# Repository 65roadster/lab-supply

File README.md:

# lab-supply
 USB Powered Lab Supply

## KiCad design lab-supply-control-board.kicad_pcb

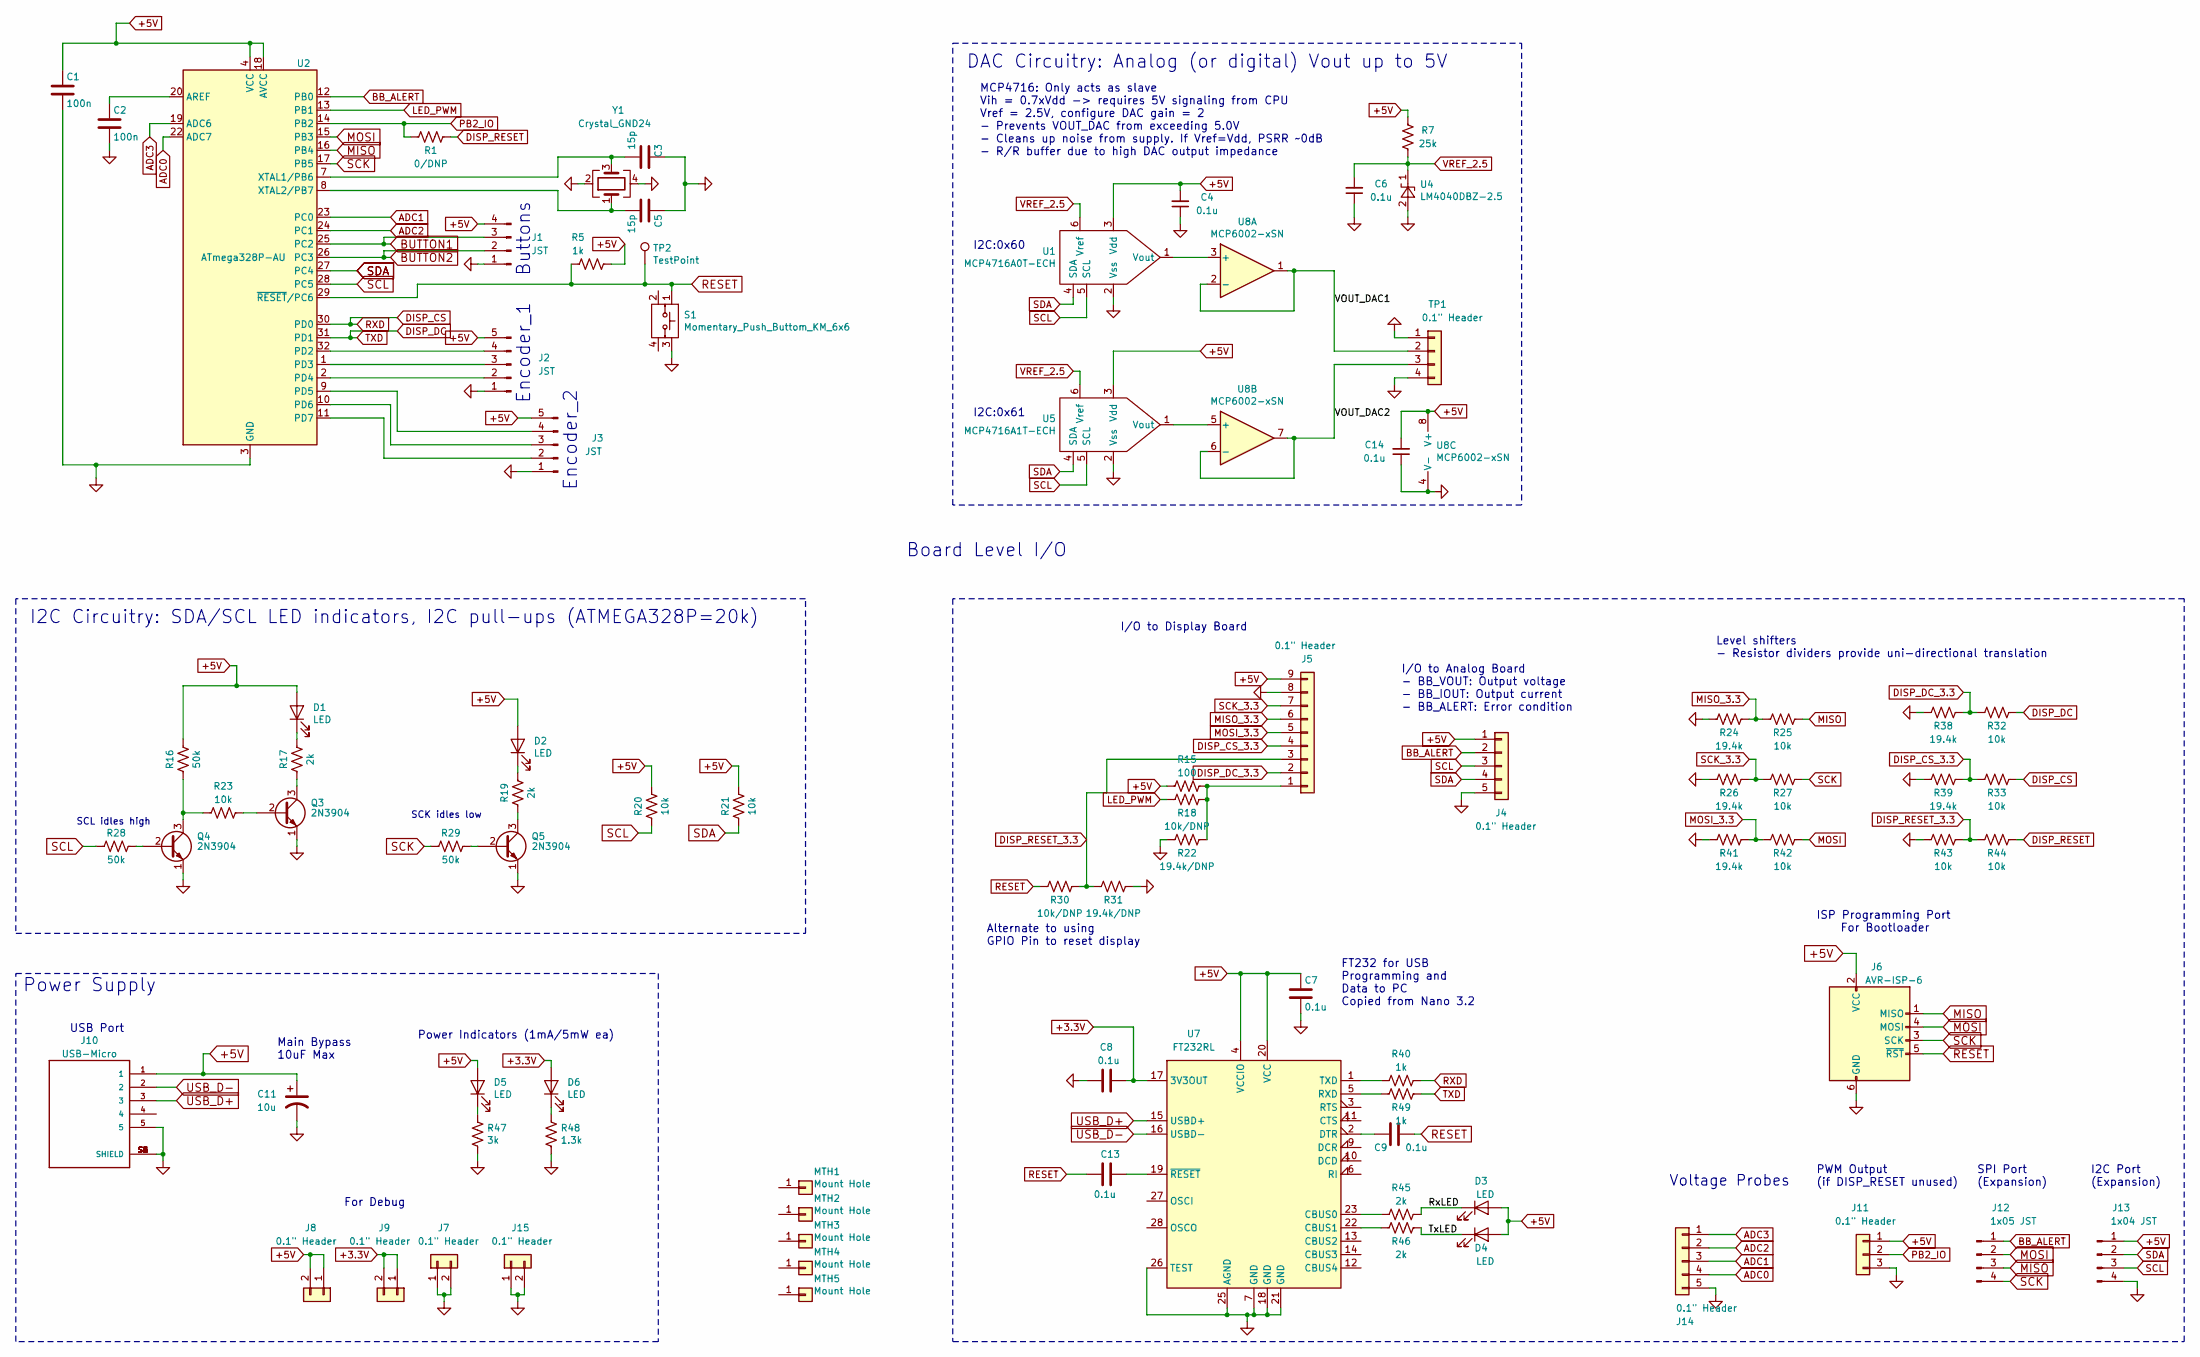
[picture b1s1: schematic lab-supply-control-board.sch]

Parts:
C1, C2: 100n; C_0805_HandSoldering
C3, C5: 15p; C_0603_HandSoldering
C4, C6, C7, C8, C9, C13, C14: 0.1u; C_0805_HandSoldering
C11: 10u; CP_Elec_4x4.5
D1, D2, D3, D4, D5, D6: LED; LED_0805_2012Metric_Pad1.15x1.40mm_HandSolder
J1: JST; JST_XH_B4B-XH-A_1x04_P2.50mm_Vertical
J2, J3: JST; JST_XH_B5B-XH-A_1x05_P2.50mm_Vertical
J4, J14: 0.1\" Header; JST_XH_B5B-XH-A_1x05_P2.50mm_Vertical
J5: 0.1\" Header; JST_XH_B9B-XH-A_1x09_P2.50mm_Vertical
J6: AVR-ISP-6; AVR-ISP-6-TH
J7, J8, J9, J15: 0.1\" Header; PinHeader_1x02_P2.54mm_Vertical
J10: USB-Micro; USB-Micro-AMPHENOL_10118194-0001LF
J11: 0.1\" Header; PinHeader_1x03_P2.54mm_Vertical
J12: 1x05 JST; JST_XH_B4B-XH-A_1x04_P2.50mm_Vertical
J13: 1x04 JST; JST_XH_B4B-XH-A_1x04_P2.50mm_Vertical
MTH1, MTH2, MTH3, MTH4, MTH5: Mount Hole; Mount-Hole-#6
Q3, Q4, Q5: 2N3904; 2N3904-SOT-23
R1: 0/DNP; R_0805_HandSoldering
R5, R40, R49: 1k; R_0805_HandSoldering
R7: 25k; R_0805_HandSoldering
R15: 100; R_0805_HandSoldering
R16, R28, R29: 50k; R_0805_HandSoldering
R17, R19, R45, R46: 2k; R_0805_HandSoldering
R18, R30: 10k/DNP; R_0805_HandSoldering
R20, R21, R23, R25, R27, R32, R33, R42, R43, R44: 10k; R_0805_HandSoldering
R22, R31: 19.4k/DNP; R_0805_HandSoldering
R24, R26, R38, R39, R41: 19.4k; R_0805_HandSoldering
R47: 3k; R_0805_HandSoldering
R48: 1.3k; R_0805_HandSoldering
S1: Momentary_Push_Buttom_KM_6x6; Momentary_Push_Button_KM_6x6
TP1: 0.1\" Header; JST_XH_B4B-XH-A_1x04_P2.50mm_Vertical
TP2: TestPoint; PinHeader_1x01_P2.54mm_Vertical
U1: MCP4716A0T-ECH; SOT-23-6_Handsoldering
U2: ATmega328P-AU; TQFP-32_7x7mm_P0.8mm
U4: LM4040DBZ-2.5; SOT-23
U5: MCP4716A1T-ECH; SOT-23-6_Handsoldering
U7: FT232RL; SSOP-28_5.3x10.2mm_P0.65mm
U8: MCP6002-xSN; SOP-8_3.9x4.9mm_P1.27mm
Y1: Crystal_GND24; Crystal_SMD_CX2016DB_2.0x1.6mm

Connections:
+3.3V: C8.2, D6.2 (A), J9.1, J9.2, U7.17 (3V3OUT)
+5V: C1.1, C4.2, C7.1, C11.1, C14.2, D1.2 (A), D2.2 (A), D3.2 (A), D4.2 (A), D5.2 (A), J1.4, J2.5, J3.5, J4.1, J5.9, J6.2 (VCC), J8.1, J8.2, J10.1, J11.1, J13.1, R5.2, R7.2, R15.1, R16.1, R20.2, R21.2, U1.3 (Vdd), U2.4 (VCC), U2.6 (VCC), U2.18 (AVCC), U5.3 (Vdd), U7.4 (VCCIO), U7.20 (VCC), U8.8 (V+)
/RxLED: D3.1 (K), R45.1
/TxLED: D4.1 (K), R46.1
/VOUT_DAC1: TP1.2, U8.1, U8.2 (-)
/VOUT_DAC2: TP1.3, U8.6 (-), U8.7
ADC0: J14.4, U2.22 (ADC7)
ADC1: J14.3, U2.23 (PC0)
ADC2: J14.2, U2.24 (PC1)
ADC3: J14.1, U2.19 (ADC6)
BB_ALERT: J4.2, J12.1, U2.12 (PB0)
BUTTON1: J1.3, U2.25 (PC2)
BUTTON2: J1.2, U2.26 (PC3)
DISP_CS: R33.2, R40.1, U2.30 (PD0)
DISP_CS_3.3: J5.4, R33.1, R39.2
DISP_DC: R32.2, R49.1, U2.31 (PD1)
DISP_DC_3.3: J5.2, R32.1, R38.2
DISP_RESET: R1.2, R44.2
DISP_RESET_3.3: J5.3, R30.2, R31.1, R43.2, R44.1
GND: C1.2, C2.2, C3.1, C4.1, C5.1, C6.1, C7.2, C8.1, C11.2, C14.1, J1.1, J2.1, J3.1, J4.5, J5.8, J6.6 (GND), J7.1, J7.2, J10.5, J10.S1 (SHIELD), J10.S2 (SHIELD), J10.S3 (SHIELD), J10.S4 (SHIELD), J10.S5 (SHIELD), J10.S6 (SHIELD), J11.3, J13.4, J14.5, J15.1, J15.2, Q3.1 (E), Q4.1 (E), Q5.1 (E), R22.1, R24.1, R26.1, R31.2, R38.1, R39.1, R41.1, R43.1, R47.2, R48.2, S1.3, TP1.1, TP1.4, U1.2 (Vss), U2.3 (GND), U2.5 (GND), U2.21 (GND), U4.2 (A), U5.2 (Vss), U7.7 (GND), U7.18 (GND), U7.21 (GND), U7.25 (AGND), U7.26 (TEST), U8.4 (V-), Y1.2, Y1.4
LED_PWM: R18.1, U2.13 (PB1)
MISO: J6.1 (MISO), J12.3, R25.2, U2.16 (PB4)
MISO_3.3: J5.6, R24.2, R25.1
MOSI: J6.4 (MOSI), J12.2, R42.2, U2.15 (PB3)
MOSI_3.3: J5.5, R41.2, R42.1
unnamed: C2.1, U2.20 (AREF)
unnamed: C3.2, U2.7 (XTAL1/PB6), Y1.3
unnamed: C5.2, U2.8 (XTAL2/PB7), Y1.1
unnamed: C9.1, U7.2 (DTR)
unnamed: C13.1, U7.19 (~RESET~)
unnamed: D1.1 (K), R17.2
unnamed: D2.1 (K), R19.2
unnamed: D5.1 (K), R47.1
unnamed: D6.1 (K), R48.1
unnamed: J2.2, U2.2 (PD4)
unnamed: J2.3, U2.1 (PD3)
unnamed: J2.4, U2.32 (PD2)
unnamed: J3.2, U2.11 (PD7)
unnamed: J3.3, U2.10 (PD6)
unnamed: J3.4, U2.9 (PD5)
unnamed: J5.1, R15.2, R18.2, R22.2
unnamed: Q3.2 (B), R23.2
unnamed: Q3.3 (C), R17.1
unnamed: Q4.2 (B), R28.2
unnamed: Q4.3 (C), R16.2, R23.1
unnamed: Q5.2 (B), R29.2
unnamed: Q5.3 (C), R19.1
unnamed: R40.2, U7.1 (TXD)
unnamed: R45.2, U7.23 (CBUS0)
unnamed: R46.2, U7.22 (CBUS1)
unnamed: R49.2, U7.5 (RXD)
unnamed: U1.1 (Vout), U8.3 (+)
unnamed: U5.1 (Vout), U8.5 (+)
PB2_IO: J11.2, R1.1, U2.14 (PB2)
RESET: C9.2, C13.2, J6.5 (~RST), R5.1, R30.1, S1.1, TP2.1, U2.29 (~RESET~/PC6)
SCK: J6.3 (SCK), J12.4, R27.2, R29.1, U2.17 (PB5)
SCK_3.3: J5.7, R26.2, R27.1
SCL: J4.3, J13.3, R20.1, R28.1, U1.5 (SCL), U2.28 (PC5), U5.5 (SCL)
SDA: J4.4, J13.2, R21.1, U1.4 (SDA), U2.27 (PC4), U5.4 (SDA)
USB_D+: J10.3, U7.15 (USBD+)
USB_D-: J10.2, U7.16 (USBD-)
VREF_2.5: C6.2, R7.1, U1.6 (Vref), U4.1 (K), U5.6 (Vref)

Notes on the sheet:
Voltage Probes
Encoder_1
Encoder_2
SCL idles high
SCK idles low
ISP Programming Port For Bootloader
DAC Circuitry: Analog (or digital) Vout up to 5V
SPI Port (Expansion)
I2C Circuitry: SDA/SCL LED indicators, I2C pull-ups (ATMEGA328P=20k)
USB Port
Board Level I/O
I2C Port (Expansion)
I/O to Display Board
MCP4716: Only acts as slave Vih = 0.7xVdd -> requires 5V signaling from CPU Vref = 2.5V, configure DAC gain = 2 - Prevents VOUT_DAC from exceeding 5.0V - Cleans up noise from supply. If Vref=Vdd, PSRR ~~0dB - R/R buffer due to high DAC output impedance
Power Indicators (1mA/5mW ea)
For Debug
PWM Output (if DISP_RESET unused)
I/O to Analog Board - BB_VOUT: Output voltage - BB_IOUT: Output current - BB_ALERT: Error condition
Level shifters - Resistor dividers provide uni-directional translation
Power Supply
Alternate to using GPIO Pin to reset display
Main Bypass 10uF Max
FT232 for USB Programming and Data to PC Copied from Nano 3.2
I2C:0x60
I2C:0x61
Buttons

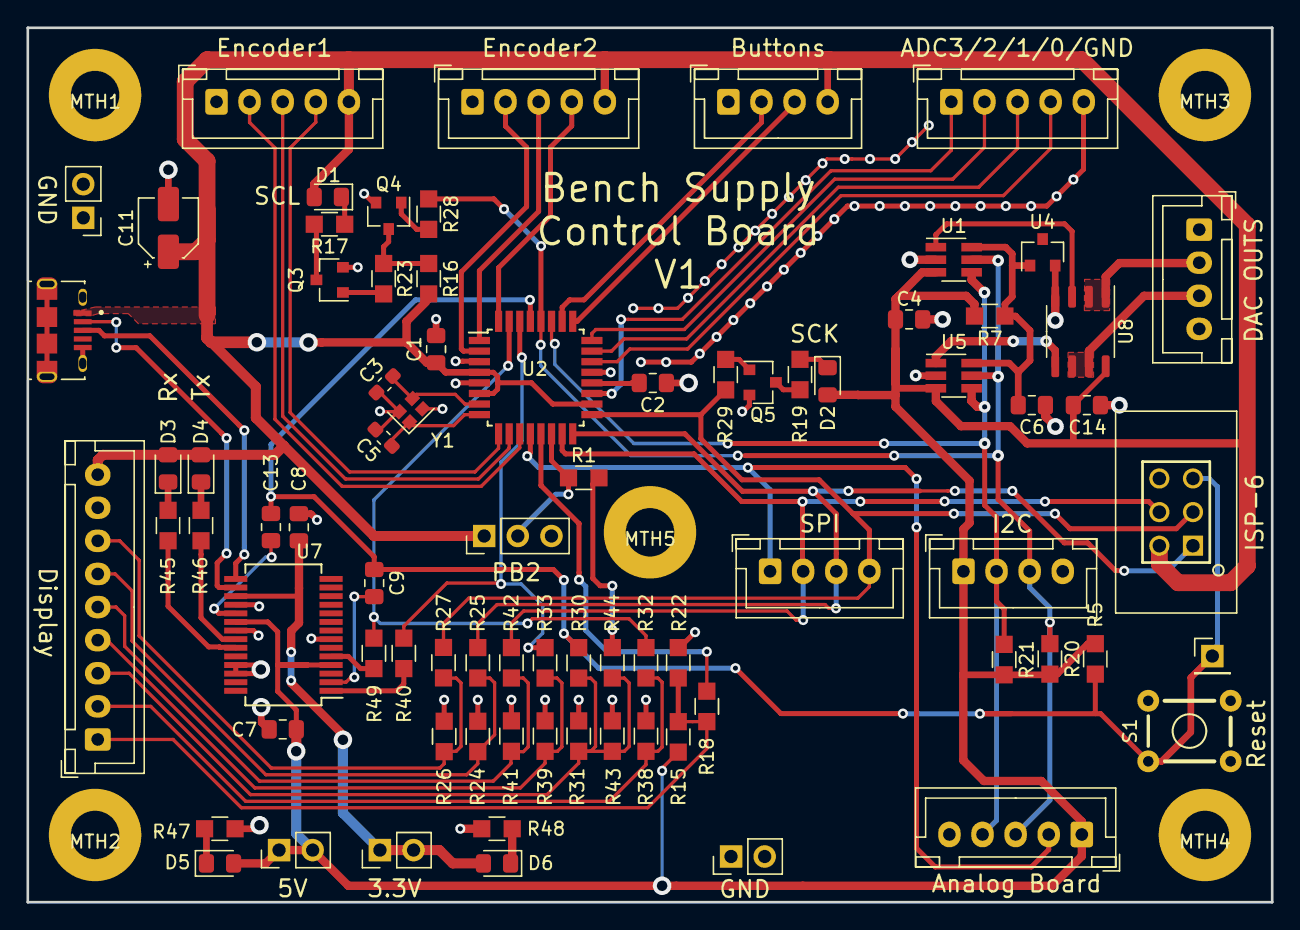
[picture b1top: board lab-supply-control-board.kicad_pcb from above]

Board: 2 copper layers, 94.0 x 66.0 mm, 85 parts (0 on the bottom side), 62 nets.

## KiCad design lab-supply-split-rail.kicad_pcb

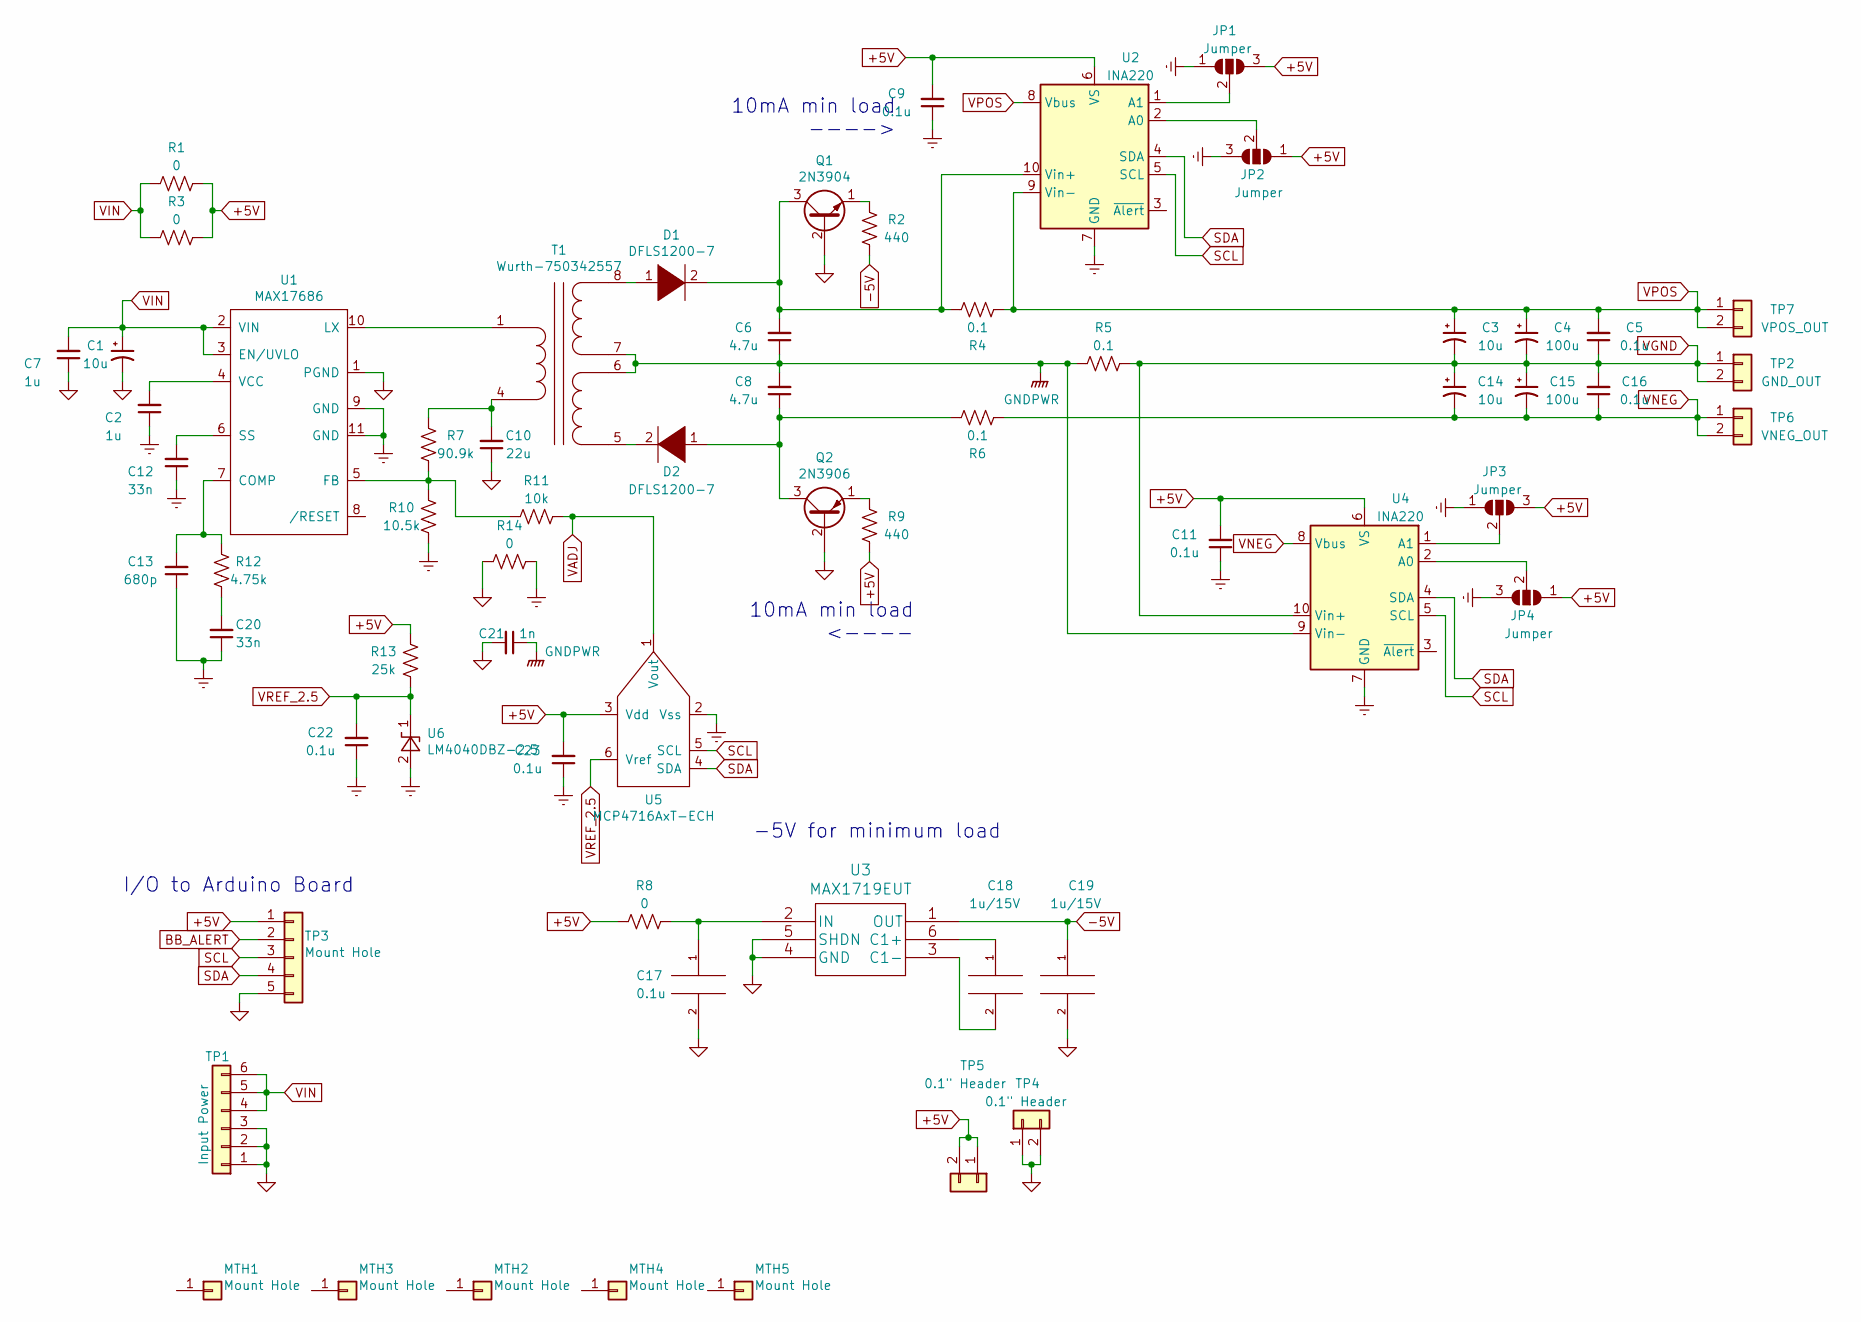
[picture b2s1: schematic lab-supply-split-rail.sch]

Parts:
C1, C3, C14: 10u; CP_Elec_4x4.5
C2, C7: 1u; C_0603_HandSoldering
C4, C15: 100u; CP_Elec_6.3x5.9
C5, C9, C11, C16, C22, C23: 0.1u; C_0603_HandSoldering
C6, C8: 4.7u; C_0603_HandSoldering
C10: 22u; C_0603_HandSoldering
C12, C20: 33n; C_0603_HandSoldering
C13: 680p; C_0603_HandSoldering
C17: 0.1u; C_0805_HandSoldering
C18, C19: 1u/15V; C_0805_HandSoldering
C21: 1n; C_0603_HandSoldering
D1, D2: DFLS1200-7; D_PowerDI-123
JP1, JP2, JP3, JP4: Jumper; SolderJumper_3_Pad
MTH1, MTH2, MTH3, MTH4, MTH5: Mount Hole; Mount-Hole-#6
Q1: 2N3904; SOT-23
Q2: 2N3906; SOT-23
R1, R3, R8, R14: 0; R_0805_HandSoldering
R2, R9: 440; R_0805_HandSoldering
R4, R5, R6: 0.1; R_2512_HandSoldering
R7: 90.9k; R_0805_HandSoldering
R10: 10.5k; R_0805_HandSoldering
R11: 10k; R_0805_HandSoldering
R12: 4.75k; R_0805_HandSoldering
R13: 25k; R_0805_HandSoldering
T1: Wurth-750342557
TP1: Input Power; PinHeader_1x06_P2.54mm_Vertical
TP2: GND_OUT; PinHeader_1x02_P2.54mm_Vertical
TP3: Mount Hole; JST_XH_B5B-XH-A_1x05_P2.50mm_Vertical
TP4, TP5: 0.1\" Header; PinHeader_1x02_P2.54mm_Vertical
TP6: VNEG_OUT; PinHeader_1x02_P2.54mm_Vertical
TP7: VPOS_OUT; PinHeader_1x02_P2.54mm_Vertical
U1: MAX17686; DFN-10-1EP_2x3mm_P0.5mm_EP0.64x2.4mm
U2, U4: INA220; VSSOP-10_3x3mm_P0.5mm
U3: MAX1719EUT; TSOT-23-6_HandSoldering
U5: MCP4716AxT-ECH; SOT-23-6_Handsoldering
U6: LM4040DBZ-2.5; SOT-23

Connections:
+5V: C9.2, C11.2, C23.2, JP1.3 (B), JP2.1 (A), JP3.3 (B), JP4.1 (A), R1.2, R3.2, R8.2, R9.1, R13.2, TP3.1, TP5.1, TP5.2, U2.6 (VS), U4.6 (VS), U5.3 (Vdd)
-5V: C19.1, R2.1, U3.1 (OUT)
Earth: C2.1, C9.1, C11.1, C12.1, C13.1, C20.1, C22.1, C23.1, JP1.1 (A), JP2.3 (B), JP3.1 (A), JP4.3 (B), R10.1, R14.2, U1.9 (GND), U1.11 (GND), U2.7 (GND), U4.7 (GND), U5.2 (Vss), U6.2 (A)
GND: C1.2, C7.1, C10.1, C17.2, C19.2, C21.2, Q1.2 (B), Q2.2 (B), R14.1, TP1.1, TP1.2, TP1.3, TP3.5, TP4.1, TP4.2, U1.1 (PGND), U3.4 (GND), U3.5 (SHDN)
GNDPWR: C6.1, C8.2, C21.1, R5.2, T1.6, T1.7, U4.9 (Vin-)
unnamed: C2.2, U1.4 (VCC)
unnamed: C6.2, D1.2 (A), Q1.3 (C), R4.2, U2.10 (Vin+)
unnamed: C8.1, D2.1 (K), Q2.3 (C), R6.2
unnamed: C10.2, R7.2, T1.4
unnamed: C12.2, U1.6 (SS)
unnamed: C13.2, R12.2, U1.7 (COMP)
unnamed: C17.1, R8.1, U3.2 (IN)
unnamed: C18.1, U3.6 (C1+)
unnamed: C18.2, U3.3 (C1-)
unnamed: C20.2, R12.1
unnamed: D1.1 (K), T1.8
unnamed: D2.2 (A), T1.5
unnamed: JP1.2 (C), U2.1 (A1)
unnamed: JP2.2 (C), U2.2 (A0)
unnamed: JP3.2 (C), U4.1 (A1)
unnamed: JP4.2 (C), U4.2 (A0)
unnamed: Q1.1 (E), R2.2
unnamed: Q2.1 (E), R9.2
unnamed: R7.1, R10.2, R11.1, U1.5 (FB)
unnamed: T1.1, U1.10 (LX)
SCL: TP3.3, U2.5 (SCL), U4.5 (SCL), U5.5 (SCL)
SDA: TP3.4, U2.4 (SDA), U4.4 (SDA), U5.4 (SDA)
VADJ: R11.2, U5.1 (Vout)
VGND: C3.2, C4.2, C5.1, C14.1, C15.1, C16.2, R5.1, TP2.1, TP2.2, U4.10 (Vin+)
VIN: C1.1, C7.2, R1.1, R3.1, TP1.4, TP1.5, TP1.6, U1.2 (VIN), U1.3 (EN/UVLO)
VNEG: C14.2, C15.2, C16.1, R6.1, TP6.1, TP6.2, U4.8 (Vbus)
VPOS: C3.1, C4.1, C5.2, R4.1, TP7.1, TP7.2, U2.8 (Vbus), U2.9 (Vin-)
VREF_2.5: C22.2, R13.1, U5.6 (Vref), U6.1 (K)

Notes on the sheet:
-5V for minimum load
10mA min load ---->
I/O to Arduino Board
10mA min load <----

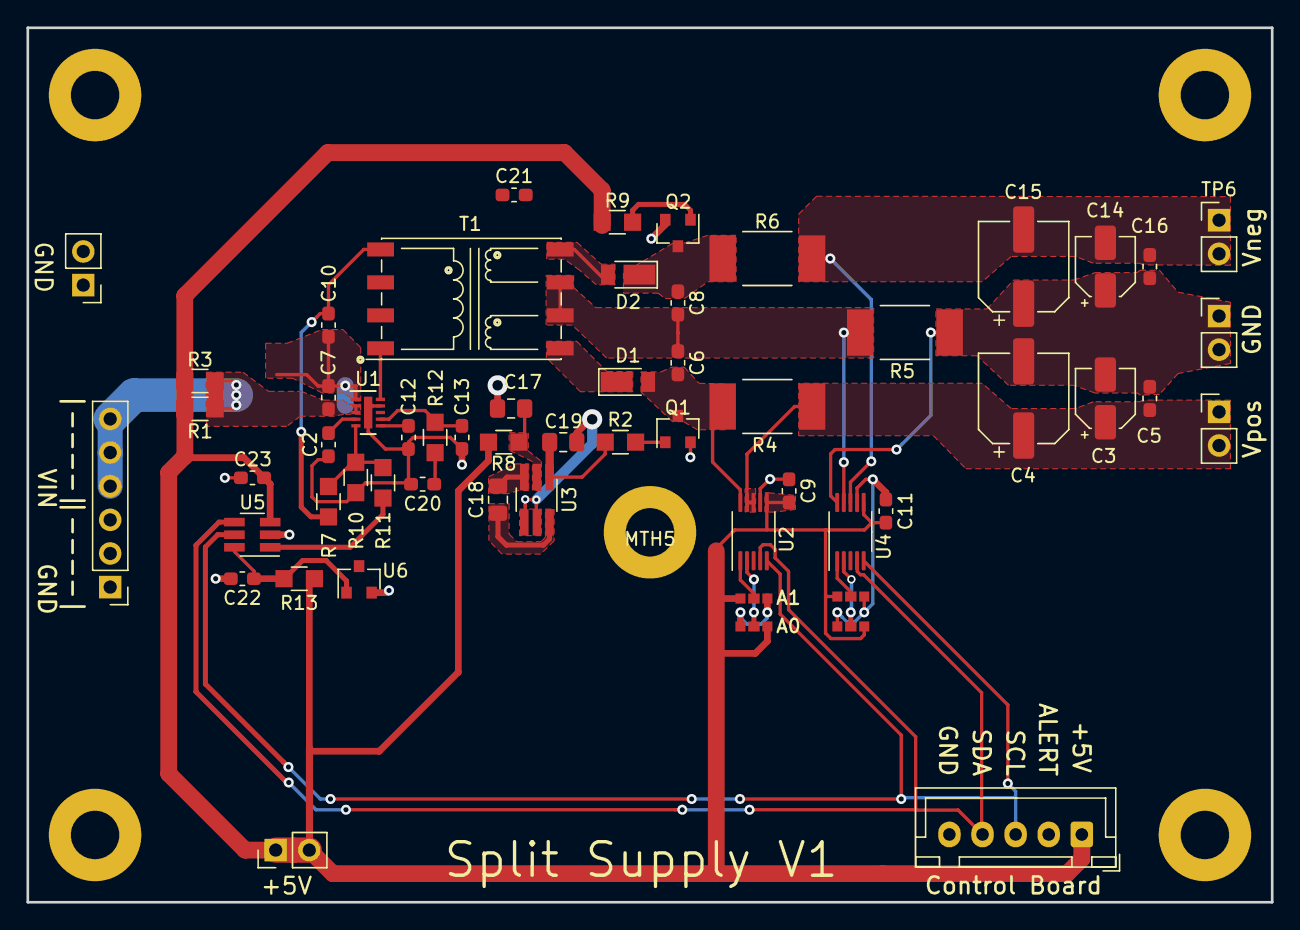
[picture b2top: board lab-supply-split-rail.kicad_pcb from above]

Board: 2 copper layers, 94.0 x 66.0 mm, 63 parts (1 on the bottom side), 33 nets.

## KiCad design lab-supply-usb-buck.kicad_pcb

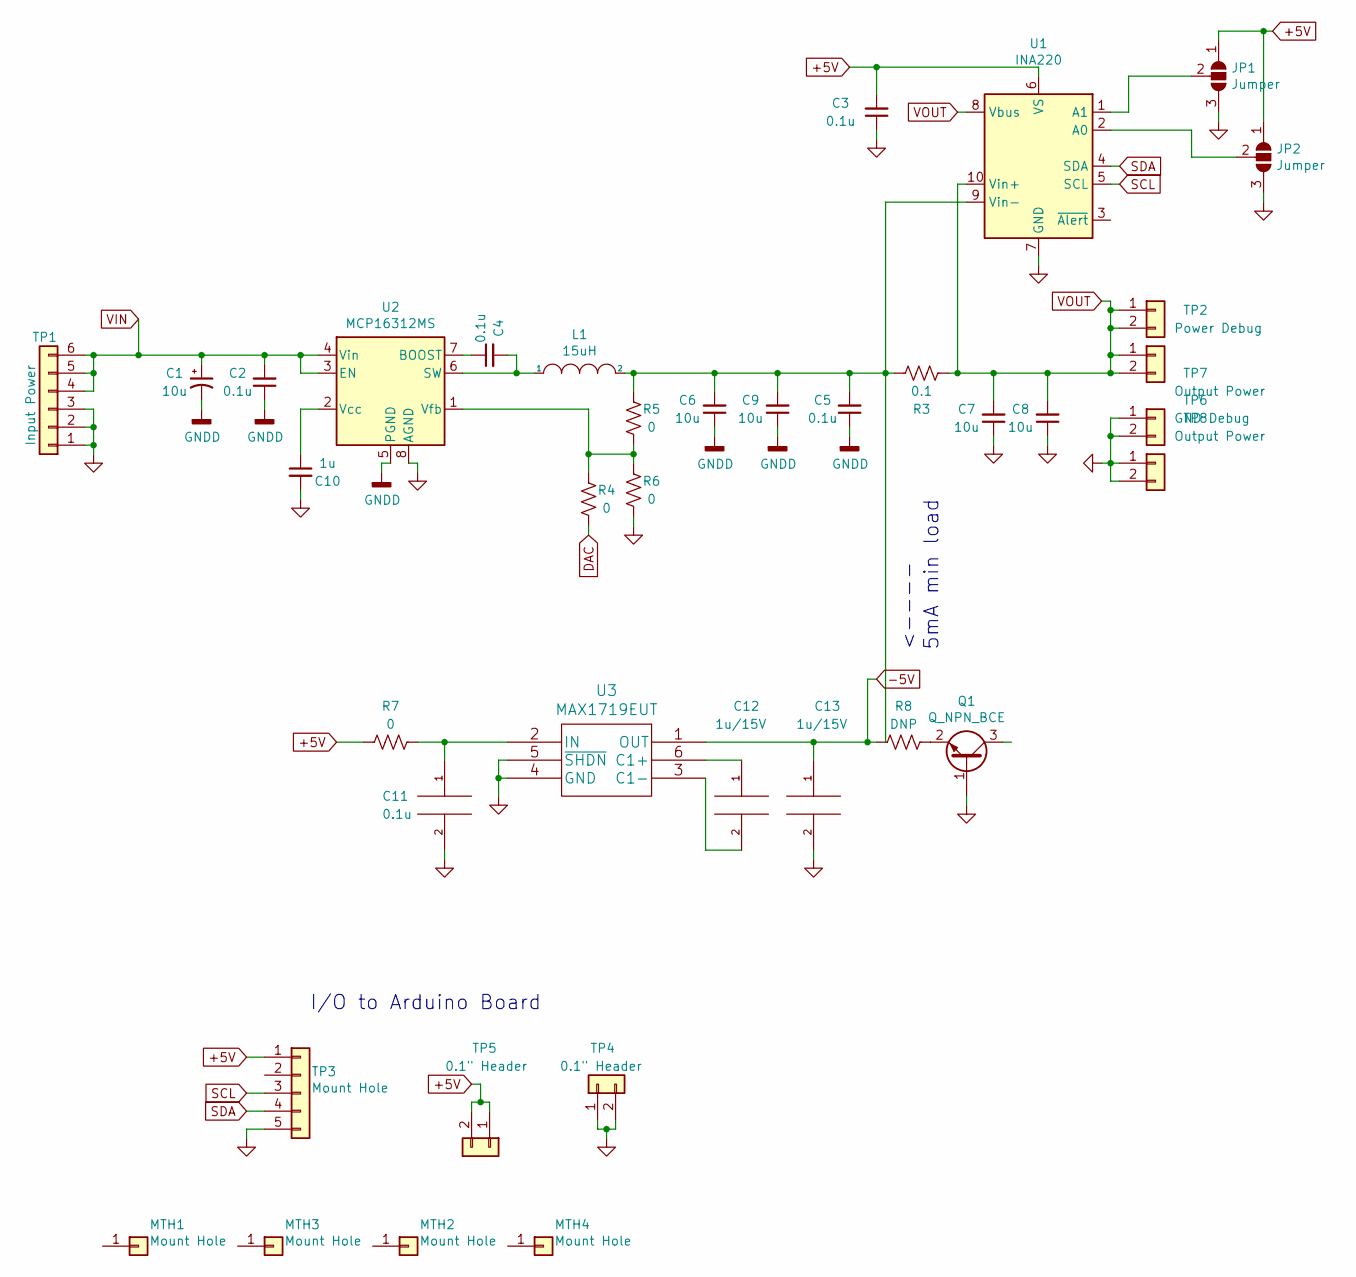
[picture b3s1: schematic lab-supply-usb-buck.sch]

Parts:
C1, C6, C7, C8, C9: 10u; C_1210_HandSoldering
C2, C4, C11: 0.1u; C_0805_HandSoldering
C3, C5: 0.1u; C_0603_HandSoldering
C10: 1u; C_0805_HandSoldering
C12, C13: 1u/15V; C_0805_HandSoldering
JP1, JP2: Jumper; SolderJumper_3_Pad
L1: 15uH; Coilcraft-XGL6060
MTH1, MTH2, MTH3, MTH4: Mount Hole; Mount-Hole-#6
Q1: Q_NPN_BCE; SOT-23
R3: 0.1; R_2512_HandSoldering
R4, R5, R6, R7: 0; R_0805_HandSoldering
R8: DNP; R_0805_HandSoldering
TP1: Input Power; PinHeader_1x06_P2.54mm_Vertical
TP2: Power Debug; PinHeader_1x02_P2.54mm_Vertical
TP3: Mount Hole; JST_XH_B5B-XH-A_1x05_P2.50mm_Vertical
TP4, TP5: 0.1\" Header; PinHeader_1x02_P2.54mm_Vertical
TP6: GND Debug; PinHeader_1x02_P2.54mm_Vertical
TP7, TP8: Output Power; PinHeader_1x02_P2.54mm_Vertical
U1: INA220; VSSOP-10_3x3mm_P0.5mm
U2: MCP16312MS; MSOP-8_3x3mm_P0.65mm
U3: MAX1719EUT; TSOT-23-6_HandSoldering

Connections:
+5V: C3.2, JP1.1 (A), JP2.1 (A), R7.2, TP3.1, TP5.1, TP5.2, U1.6 (VS)
-5V: C13.1, R8.2, U3.1 (OUT)
GND: C3.1, C7.1, C8.1, C10.2, C11.2, C13.2, JP1.3 (B), JP2.3 (B), Q1.1 (B), R6.1, TP1.1, TP1.2, TP1.3, TP3.5, TP4.1, TP4.2, TP7.1, TP7.2, TP8.1, TP8.2, U1.7 (GND), U2.8 (AGND), U3.4 (GND), U3.5 (~SHDN)
GNDD: C1.2, C2.1, C5.1, C6.1, C9.1, U2.5 (PGND)
unnamed: C4.1, U2.7 (BOOST)
unnamed: C4.2, L1.1, U2.6 (SW)
unnamed: C5.2, C6.2, C9.2, L1.2, R3.2, R5.2, U1.9 (Vin-)
unnamed: C10.1, U2.2 (Vcc)
unnamed: C11.1, R7.1, U3.2 (IN)
unnamed: C12.1, U3.6 (C1+)
unnamed: C12.2, U3.3 (C1-)
unnamed: JP1.2 (C), U1.1 (A1)
unnamed: JP2.2 (C), U1.2 (A0)
unnamed: Q1.2 (E), R8.1
unnamed: R4.2, R5.1, R6.2, U2.1 (Vfb)
SCL: TP3.3, U1.5 (SCL)
SDA: TP3.4, U1.4 (SDA)
VIN: C1.1, C2.2, TP1.4, TP1.5, TP1.6, U2.3 (EN), U2.4 (Vin)
VOUT: C7.2, C8.2, R3.1, TP2.1, TP2.2, TP6.1, TP6.2, U1.8 (Vbus), U1.10 (Vin+)

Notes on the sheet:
I/O to Arduino Board
<---- 5mA min load

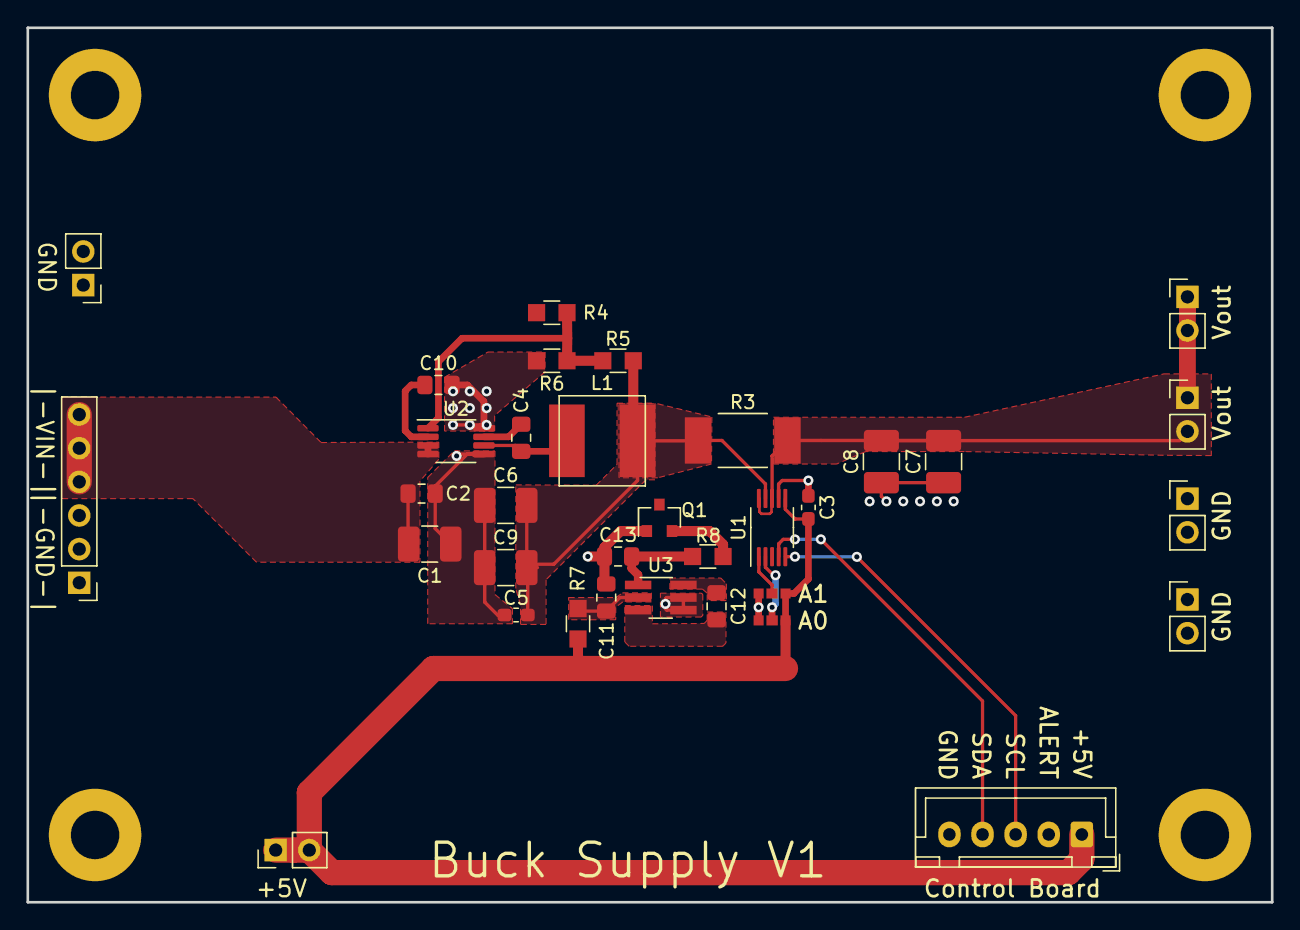
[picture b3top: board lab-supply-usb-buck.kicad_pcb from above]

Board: 2 copper layers, 94.0 x 66.0 mm, 38 parts (0 on the bottom side), 19 nets.

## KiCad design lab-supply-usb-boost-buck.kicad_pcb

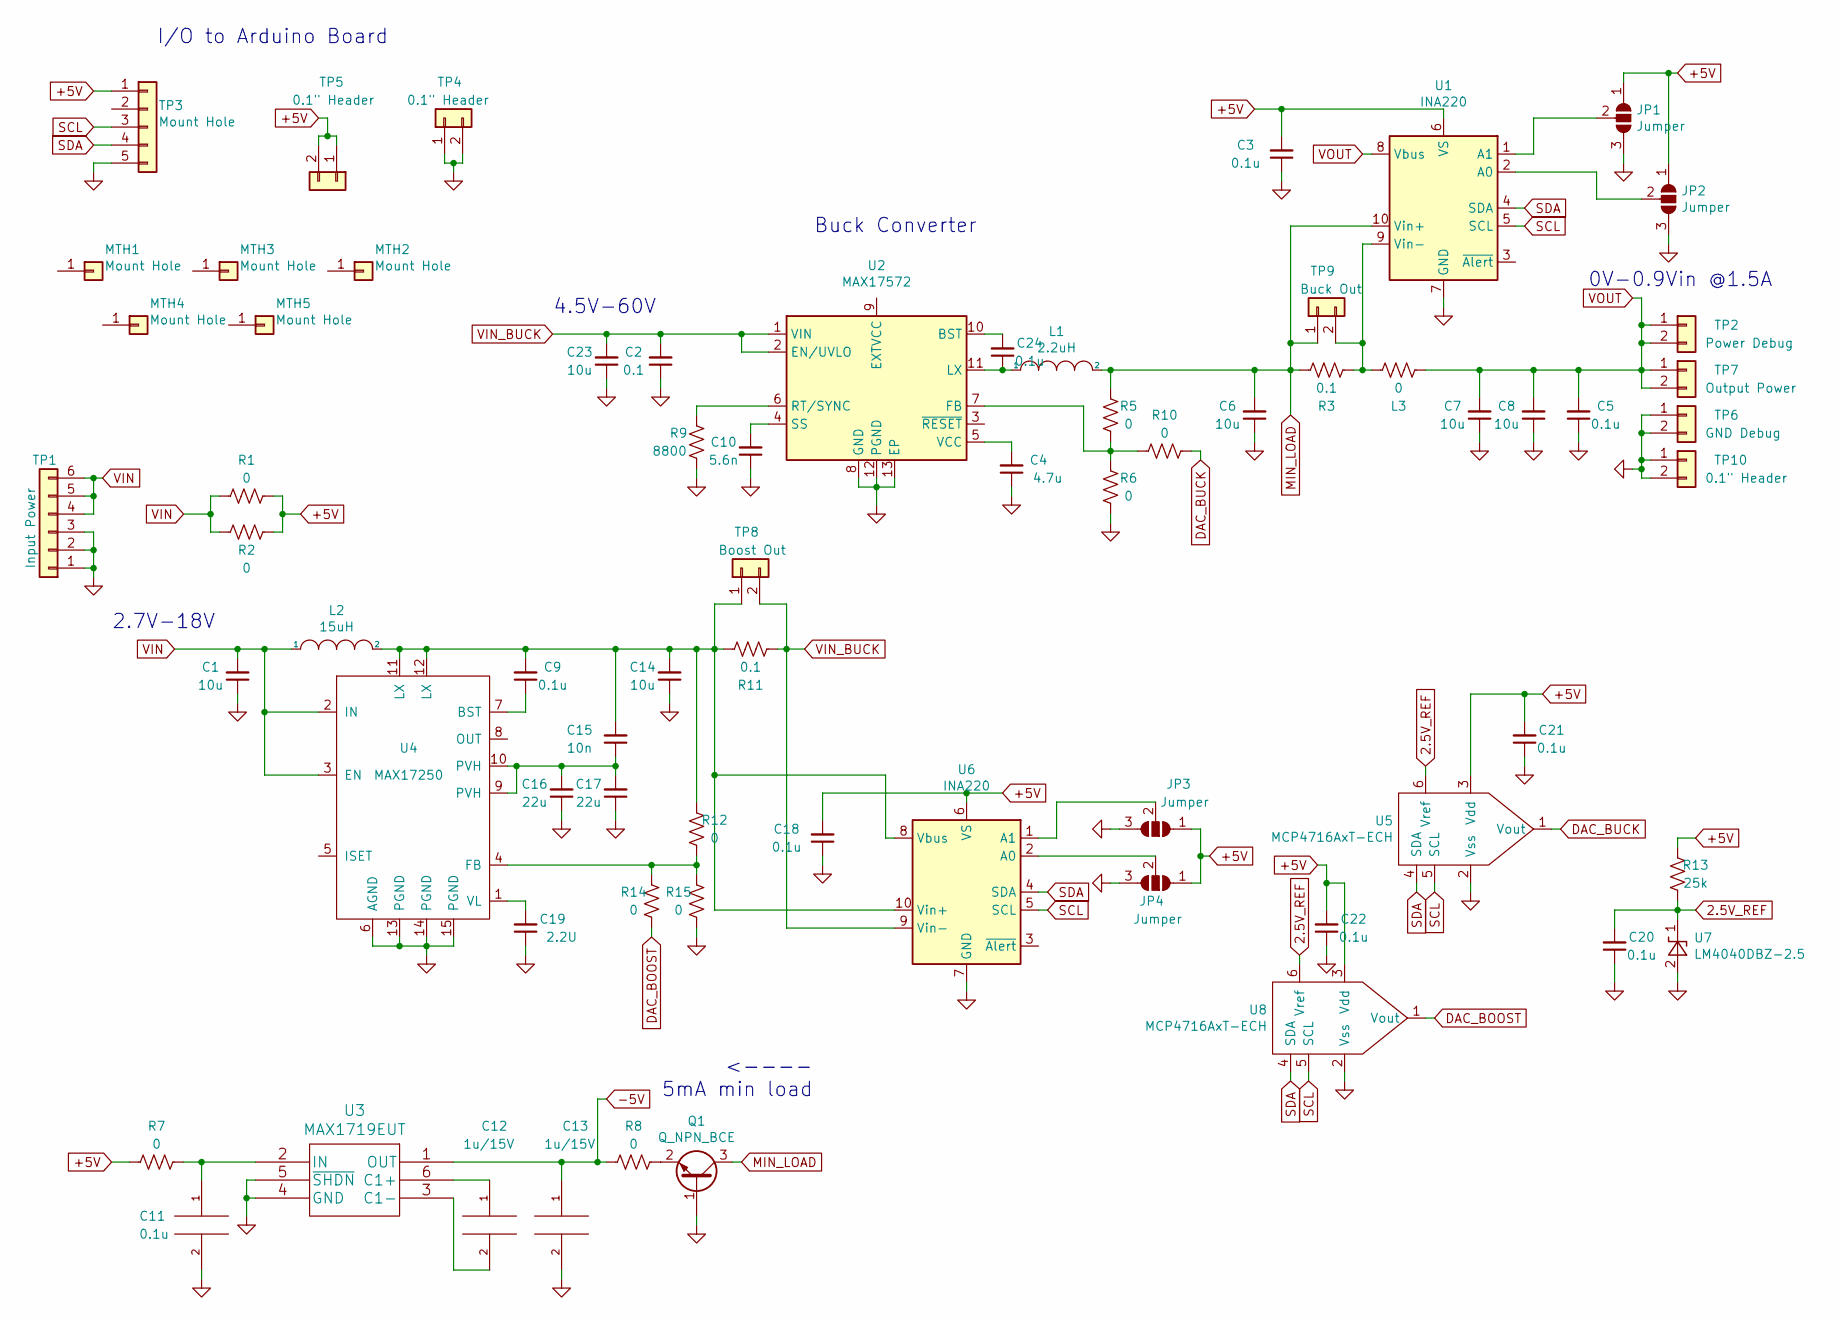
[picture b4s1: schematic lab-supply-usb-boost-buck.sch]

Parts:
C1, C6, C7, C8, C14, C23: 10u; C_1210_HandSoldering
C2: 0.1; C_0805_HandSoldering
C3, C5, C9, C11, C18, C20, C21, C22, C24: 0.1u; C_0805_HandSoldering
C4: 4.7u; C_0805_HandSoldering
C10: 5.6n; C_0805_HandSoldering
C12, C13: 1u/15V; C_0805_HandSoldering
C15: 10n; C_0603_HandSoldering
C16, C17: 22u; C_1210_HandSoldering
C19: 2.2U; C_0805_HandSoldering
JP1, JP2, JP3, JP4: Jumper; SolderJumper_3_Pad
L1: 2.2uH; Coilcraft-XFL4020
L2: 15uH; Coilcraft-XAL4040
L3: 0; R_0805_HandSoldering
MTH1, MTH2, MTH3, MTH4, MTH5: Mount Hole; Mount-Hole-#6
Q1: Q_NPN_BCE; SOT-23
R1, R2, R5, R6, R7, R8, R10, R12, R14, R15: 0; R_0805_HandSoldering
R3, R11: 0.1; R_2512_HandSoldering
R9: 8800; R_0805_HandSoldering
R13: 25k; R_0805_HandSoldering
TP1: Input Power; PinHeader_1x06_P2.54mm_Vertical
TP2: Power Debug; PinHeader_1x02_P2.54mm_Vertical
TP3: Mount Hole; JST_XH_B5B-XH-A_1x05_P2.50mm_Vertical
TP4, TP5, TP10: 0.1\" Header; PinHeader_1x02_P2.54mm_Vertical
TP6: GND Debug; PinHeader_1x02_P2.54mm_Vertical
TP7: Output Power; PinHeader_1x02_P2.54mm_Vertical
TP8: Boost Out; PinHeader_1x02_P2.54mm_Vertical
TP9: Buck Out; PinHeader_1x02_P2.54mm_Vertical
U1, U6: INA220; VSSOP-10_3x3mm_P0.5mm
U2: MAX17572; DFN-12-1EP_3x3mm_P0.5mm_EP2.05x2.86mm
U3: MAX1719EUT; TSOT-23-6_HandSoldering
U4: MAX17250; DFN-14-1EP_3x3mm_P0.4mm_EP1.78x2.35mm-6mil-DRC
U5, U8: MCP4716AxT-ECH; SOT-23-6_Handsoldering
U7: LM4040DBZ-2.5; SOT-23

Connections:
2.5V_REF: C20.2, R13.1, U5.6 (Vref), U7.1 (K), U8.6 (Vref)
+5V: C3.2, C18.2, C21.2, C22.2, JP1.1 (A), JP2.1 (A), JP3.1 (A), JP4.1 (A), R1.1, R2.1, R7.2, R13.2, TP3.1, TP5.1, TP5.2, U1.6 (VS), U5.3 (Vdd), U6.6 (VS), U8.3 (Vdd)
-5V: C13.1, R8.2, U3.1 (OUT)
DAC_BOOST: R14.2, U8.1 (Vout)
DAC_BUCK: R10.2, U5.1 (Vout)
GND: C1.1, C2.1, C3.1, C4.1, C5.1, C6.1, C7.1, C8.1, C10.1, C11.2, C13.2, C14.1, C16.1, C17.1, C18.1, C19.1, C20.1, C21.1, C22.1, C23.1, JP1.3 (B), JP2.3 (B), JP3.3 (B), JP4.3 (B), Q1.1 (B), R6.1, R9.1, R15.1, TP1.1, TP1.2, TP1.3, TP3.5, TP4.1, TP4.2, TP7.1, TP7.2, TP10.1, TP10.2, U1.7 (GND), U2.8 (GND), U2.12 (PGND), U2.13 (EP), U3.4 (GND), U3.5 (~SHDN), U4.6 (AGND), U4.13 (PGND), U4.14 (PGND), U4.15 (PGND), U5.2 (Vss), U6.7 (GND), U7.2 (A), U8.2 (Vss)
MIN_LOAD: C6.2, L1.2, Q1.3 (C), R3.2, R5.2, TP9.1, U1.10 (Vin+)
unnamed: C4.2, U2.5 (VCC)
unnamed: C9.1, U4.7 (BST)
unnamed: C10.2, U2.4 (SS)
unnamed: C11.1, R7.1, U3.2 (IN)
unnamed: C12.1, U3.6 (C1+)
unnamed: C12.2, U3.3 (C1-)
unnamed: C9.2, C14.2, C15.2, L2.2, R11.2, R12.2, TP8.1, U4.11 (LX), U4.12 (LX), U6.8 (Vbus), U6.10 (Vin+)
unnamed: C15.1, C16.2, C17.2, U4.9 (PVH), U4.10 (PVH)
unnamed: C19.2, U4.1 (VL)
unnamed: C24.1, L1.1, U2.11 (LX)
unnamed: C24.2, U2.10 (BST)
unnamed: JP1.2 (C), U1.1 (A1)
unnamed: JP2.2 (C), U1.2 (A0)
unnamed: JP3.2 (C), U6.1 (A1)
unnamed: JP4.2 (C), U6.2 (A0)
unnamed: L3.2, R3.1, TP9.2, U1.9 (Vin-)
unnamed: Q1.2 (E), R8.1
unnamed: R9.2, U2.6 (RT/SYNC)
unnamed: R5.1, R6.2, R10.1, U2.7 (FB)
unnamed: R12.1, R14.1, R15.2, U4.4 (FB)
SCL: TP3.3, U1.5 (SCL), U5.5 (SCL), U6.5 (SCL), U8.5 (SCL)
SDA: TP3.4, U1.4 (SDA), U5.4 (SDA), U6.4 (SDA), U8.4 (SDA)
VIN: C1.2, L2.1, R1.2, R2.2, TP1.4, TP1.5, TP1.6, U4.2 (IN), U4.3 (EN)
VIN_BUCK: C2.2, C23.2, R11.1, TP8.2, U2.1 (VIN), U2.2 (EN/UVLO), U6.9 (Vin-)
VOUT: C5.2, C7.2, C8.2, L3.1, TP2.1, TP2.2, TP6.1, TP6.2, U1.8 (Vbus)

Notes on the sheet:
I/O to Arduino Board
<---- 5mA min load
4.5V-60V
Buck Converter
0V-0.9Vin @1.5A
2.7V-18V

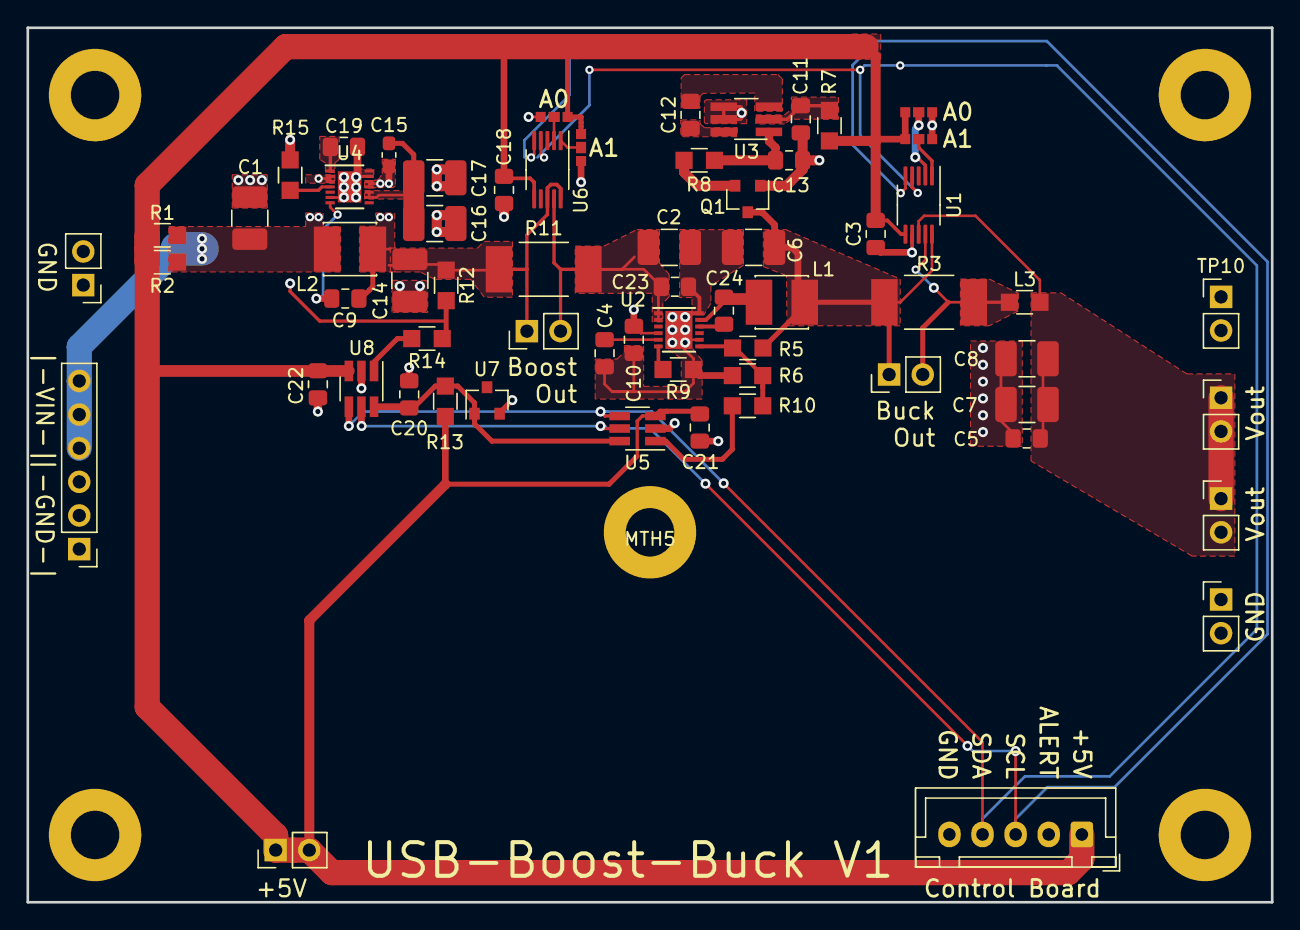
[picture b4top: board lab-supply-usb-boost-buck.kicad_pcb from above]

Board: 2 copper layers, 94.0 x 66.0 mm, 69 parts (0 on the bottom side), 32 nets.
